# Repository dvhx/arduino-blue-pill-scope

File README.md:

# arduino-blue-pill-scope
860kSPS USB scope made from Blue Pill using Arduino IDE

(this version have only first 2 voltage ranges populated)

I also made App in lazarus that interfaces the scope and shows curves:

# Revisions

1. First working 860kSPS DMA but dividers were unwisely plced on 5V rail which real world USB cables and 30mA of F103 pulled down to 4.6 and not in a nice consistent way, the noise was around 100mV, it was unusable.
2. Dividers moved to 3V3 rail which stabilized it, some resistor values needed to be adjusted to get output back into ADC range. Added app.

# Conclusion

It works, it's usable, it's more stable than DSO-138. If I were to make a PCB or version 2.0 I would choose STM variant that has separate analog ground and separate vref pin.

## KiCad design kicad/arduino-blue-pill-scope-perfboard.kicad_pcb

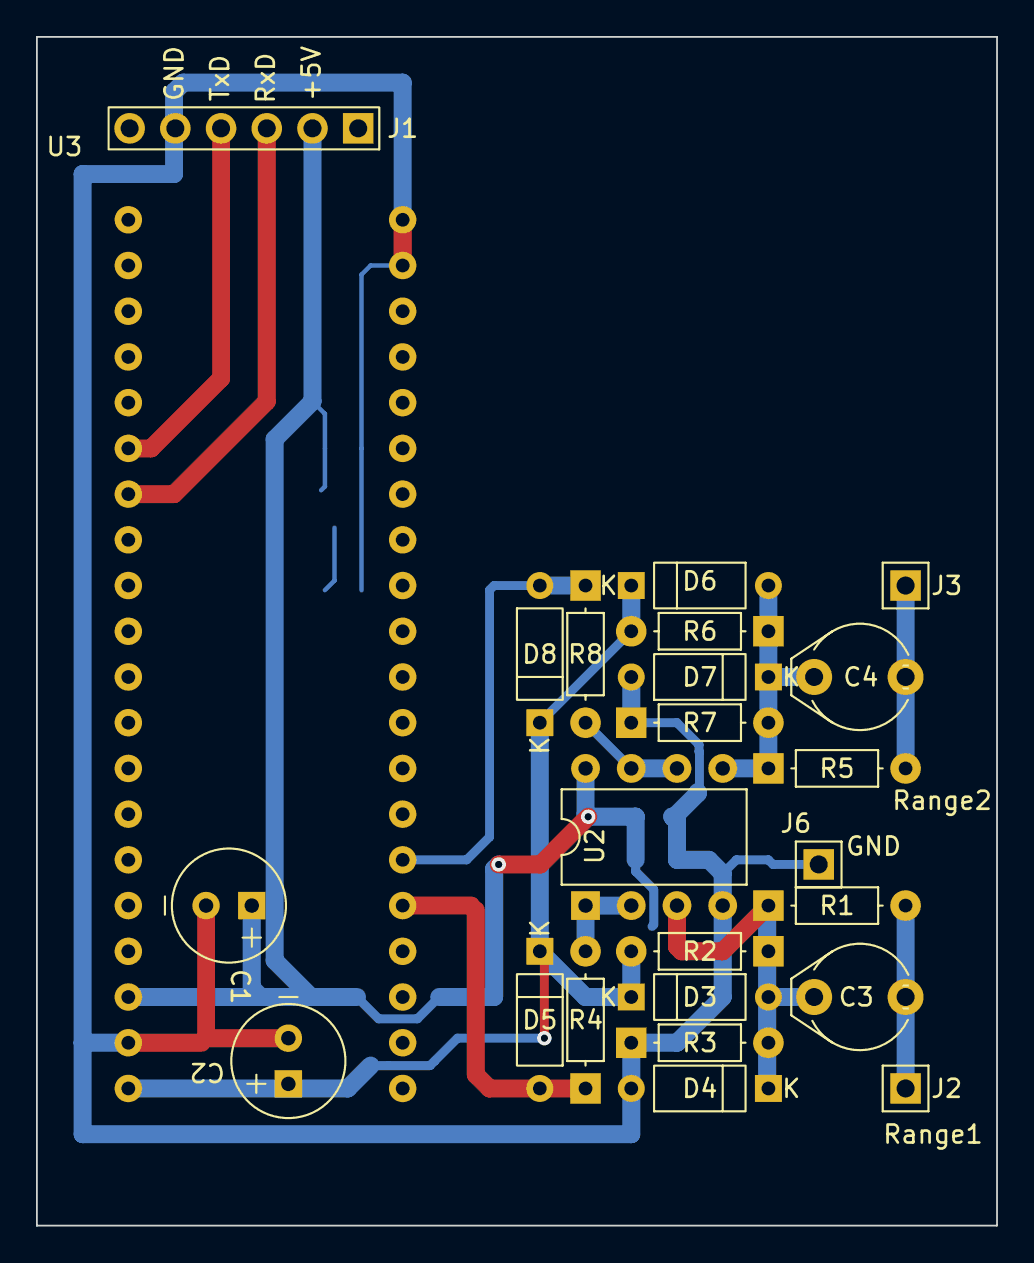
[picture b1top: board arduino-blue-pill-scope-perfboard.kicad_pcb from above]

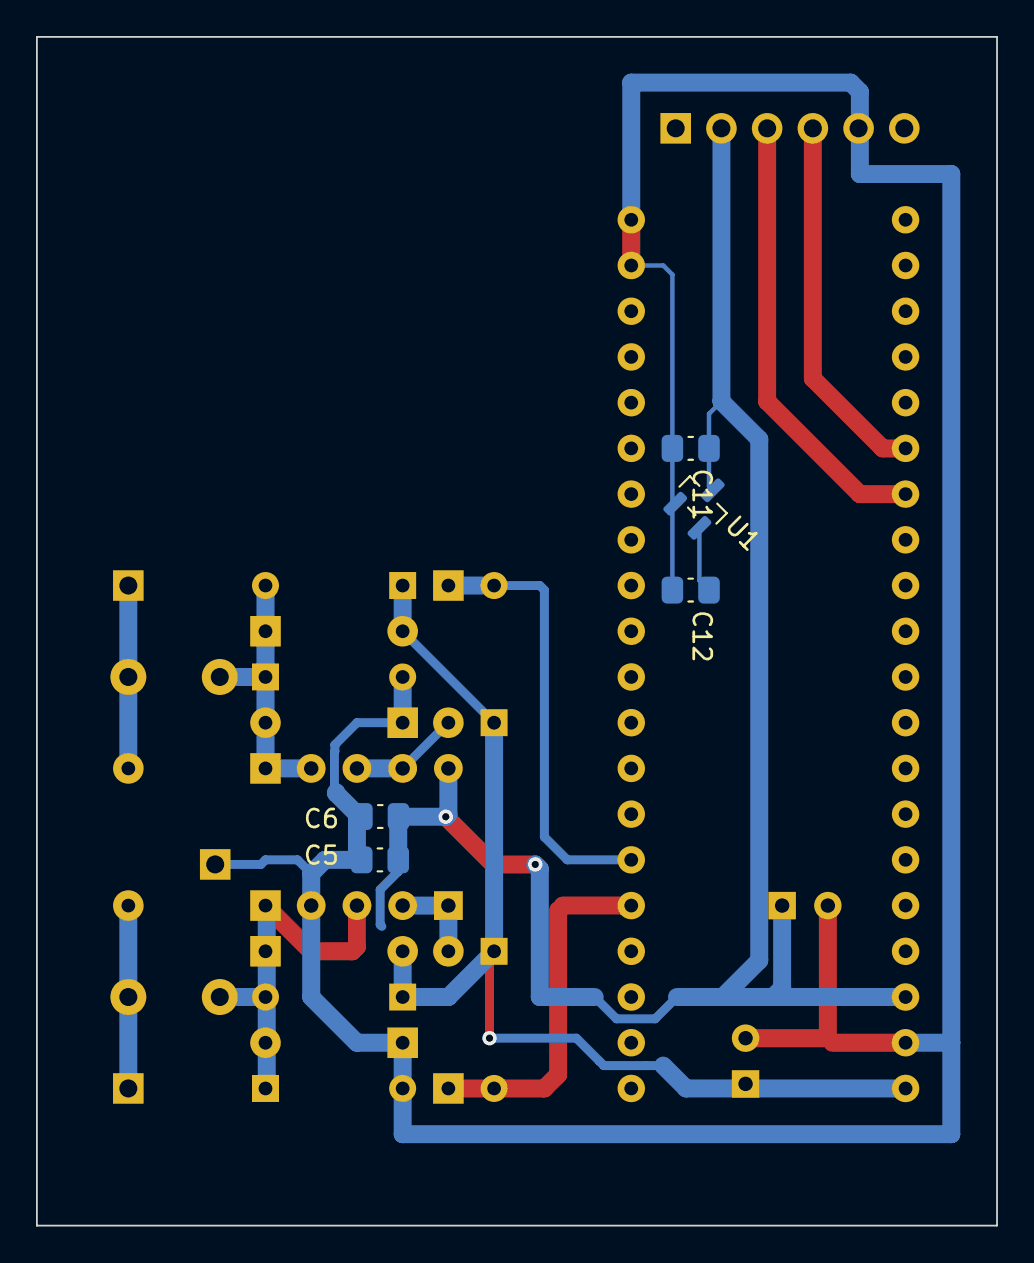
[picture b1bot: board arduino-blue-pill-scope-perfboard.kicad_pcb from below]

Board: 4 copper layers, 53.3 x 66.0 mm, 29 parts (5 on the bottom side), 14 nets.

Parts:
C1: 220u; C_polarized_D6.35mm_H5.65mm_P2.54mm
C2: 33u; C_polarized_D6.35mm_H5.65mm_P2.54mm
C3, C4: 5p; C_variable
C5: 100n; C_0805
C6, C11, C12: 10u; C_0805
D3, D4, D5, D6, D7, D8: 1N914; D_DO-41
J1: Header_1x6_male; Header_1x6_male_upright
J2, J3, J6: Header_1x1_male; Header_1x1_male_upright
R1: 5M6; R_0.25W
R2, R3, R5, R7: 1M; R_0.25W
R4, R8: 150; R_0.25W
R6: 8M2; R_0.25W
U1: ME6209A30; SOT23-GOI
U2: LM358; DIP-8_W7.62mm
U3: BluePill_STM32F103C8T6

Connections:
3V0: C12.1, U1.O
3V3: C2.P, D3.K, D5.K, D6.K, D8.K, R2.2, R6.2, U3.20 (3V3)
5V: C1.P, C5.1, C6.1, C11.1, J1.2, U1.I, U2.8 (V+), U3.18 (5V)
GND: C1.N, C2.N, C5.2, C6.2, C11.2, C12.2, D4.A, D7.A, J1.5, J6.1, R3.1, R7.1, U1.G, U2.4 (V-), U3.19 (GND), U3.39 (GND), U3.40 (GND)
unnamed: C3.1, J2.1, R1.2
unnamed: C3.2, D3.A, D4.K, R1.1, R2.1, R3.2, U2.3 (+)
unnamed: C4.1, J3.1, R5.2
unnamed: C4.2, D6.A, D7.K, R5.1, R6.1, R7.2, U2.5 (+)
unnamed: R4.2, U2.1, U2.2 (-)
unnamed: R8.2, U2.6 (-), U2.7
RANGE1: D5.A, R4.1, U3.25 (A0)
RANGE2: D8.A, R8.1, U3.26 (A1)
RxD: J1.3, U3.7 (A10)
TxD: J1.4, U3.6 (A9)

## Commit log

2025-02-22 Added app
2025-02-22 Updated arduino code
2025-02-22 Updated images
2025-02-22 Updated kicad project
2025-02-22 Added gitignore and updated readme
